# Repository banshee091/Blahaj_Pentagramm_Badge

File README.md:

# Blahaj_Pentagramm_Badge

Firmware:

Build WLED (https://github.com/Aircoookie/WLED) using PlatformIO with the following Environment using the Buildflags for BME280 and PIR:

```
[env:d1_mini]
...
build_flags = ${common.build_flags_esp8266} -D USERMOD_BME280 -D USERMOD_PIRSWITCH -D PIR_SENSOR_PIN=13
...
```

Configuration:
```
LED Preferences: 
    -> Length = 15
    -> GPIO = 14
Usermods:
    -> SDA = 4
    -> SCL = 5
    -> Enabled

    Reboot
```

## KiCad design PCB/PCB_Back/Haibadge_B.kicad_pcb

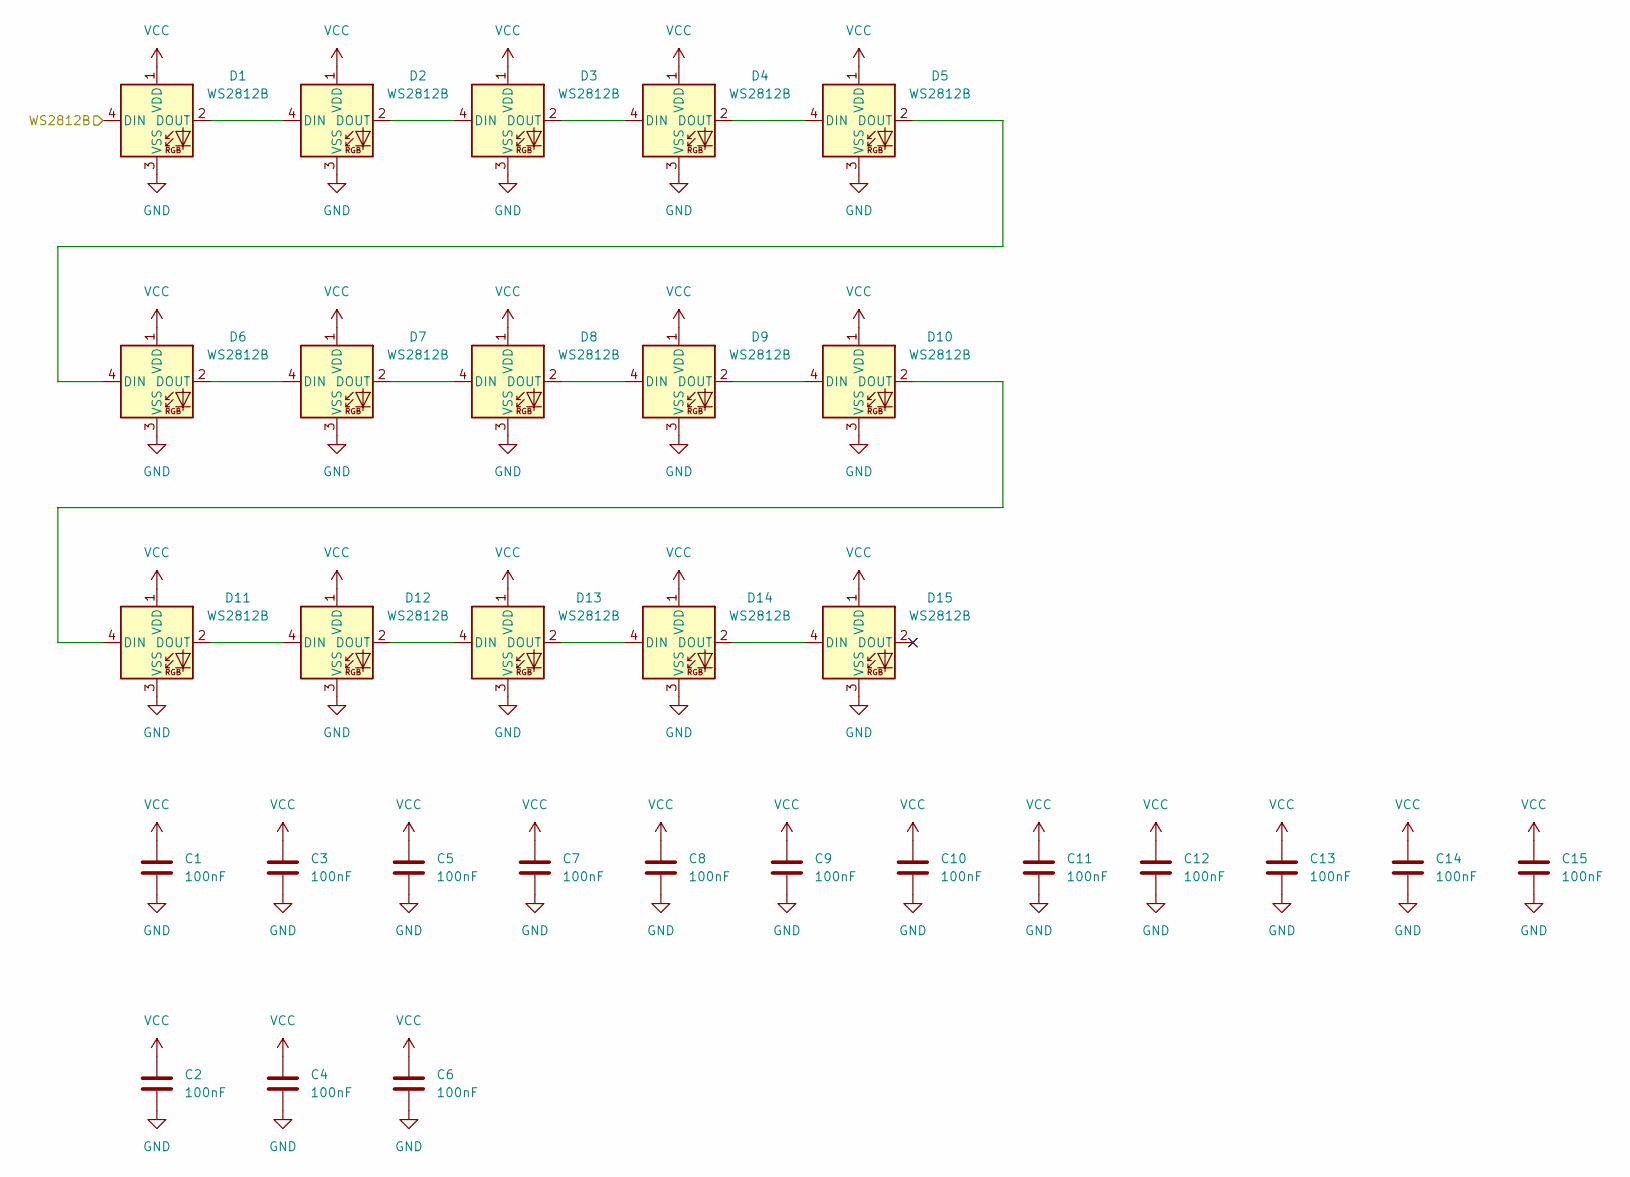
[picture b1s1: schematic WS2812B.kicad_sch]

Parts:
C1, C2, C3, C4, C5, C6, C7, C8, C9, C10, C11, C12, C13, C14, C15: 100nF; C_0805_2012Metric
D1, D2, D3, D4, D5, D6, D7, D8, D9, D10, D11, D12, D13, D14, D15: WS2812B; LED_WS2812B_PLCC4_5.0x5.0mm_P3.2mm

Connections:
/WS2812B/WS2812B: D1.4 (DIN); also elsewhere on the board
GND: C1.2, C2.2, C3.2, C4.2, C5.2, C6.2, C7.2, C8.2, C9.2, C10.2, C11.2, C12.2, C13.2, C14.2, C15.2, D1.3 (VSS), D2.3 (VSS), D3.3 (VSS), D4.3 (VSS), D5.3 (VSS), D6.3 (VSS), D7.3 (VSS), D8.3 (VSS), D9.3 (VSS), D10.3 (VSS), D11.3 (VSS), D12.3 (VSS), D13.3 (VSS), D14.3 (VSS), D15.3 (VSS); also elsewhere on the board
unnamed: D1.2 (DOUT), D2.4 (DIN)
unnamed: D2.2 (DOUT), D3.4 (DIN)
unnamed: D3.2 (DOUT), D4.4 (DIN)
unnamed: D4.2 (DOUT), D5.4 (DIN)
unnamed: D5.2 (DOUT), D6.4 (DIN)
unnamed: D6.2 (DOUT), D7.4 (DIN)
unnamed: D7.2 (DOUT), D8.4 (DIN)
unnamed: D8.2 (DOUT), D9.4 (DIN)
unnamed: D9.2 (DOUT), D10.4 (DIN)
unnamed: D10.2 (DOUT), D11.4 (DIN)
unnamed: D11.2 (DOUT), D12.4 (DIN)
unnamed: D12.2 (DOUT), D13.4 (DIN)
unnamed: D13.2 (DOUT), D14.4 (DIN)
unnamed: D14.2 (DOUT), D15.4 (DIN)
VCC: C1.1, C2.1, C3.1, C4.1, C5.1, C6.1, C7.1, C8.1, C9.1, C10.1, C11.1, C12.1, C13.1, C14.1, C15.1, D1.1 (VDD), D2.1 (VDD), D3.1 (VDD), D4.1 (VDD), D5.1 (VDD), D6.1 (VDD), D7.1 (VDD), D8.1 (VDD), D9.1 (VDD), D10.1 (VDD), D11.1 (VDD), D12.1 (VDD), D13.1 (VDD), D14.1 (VDD), D15.1 (VDD); also elsewhere on the board

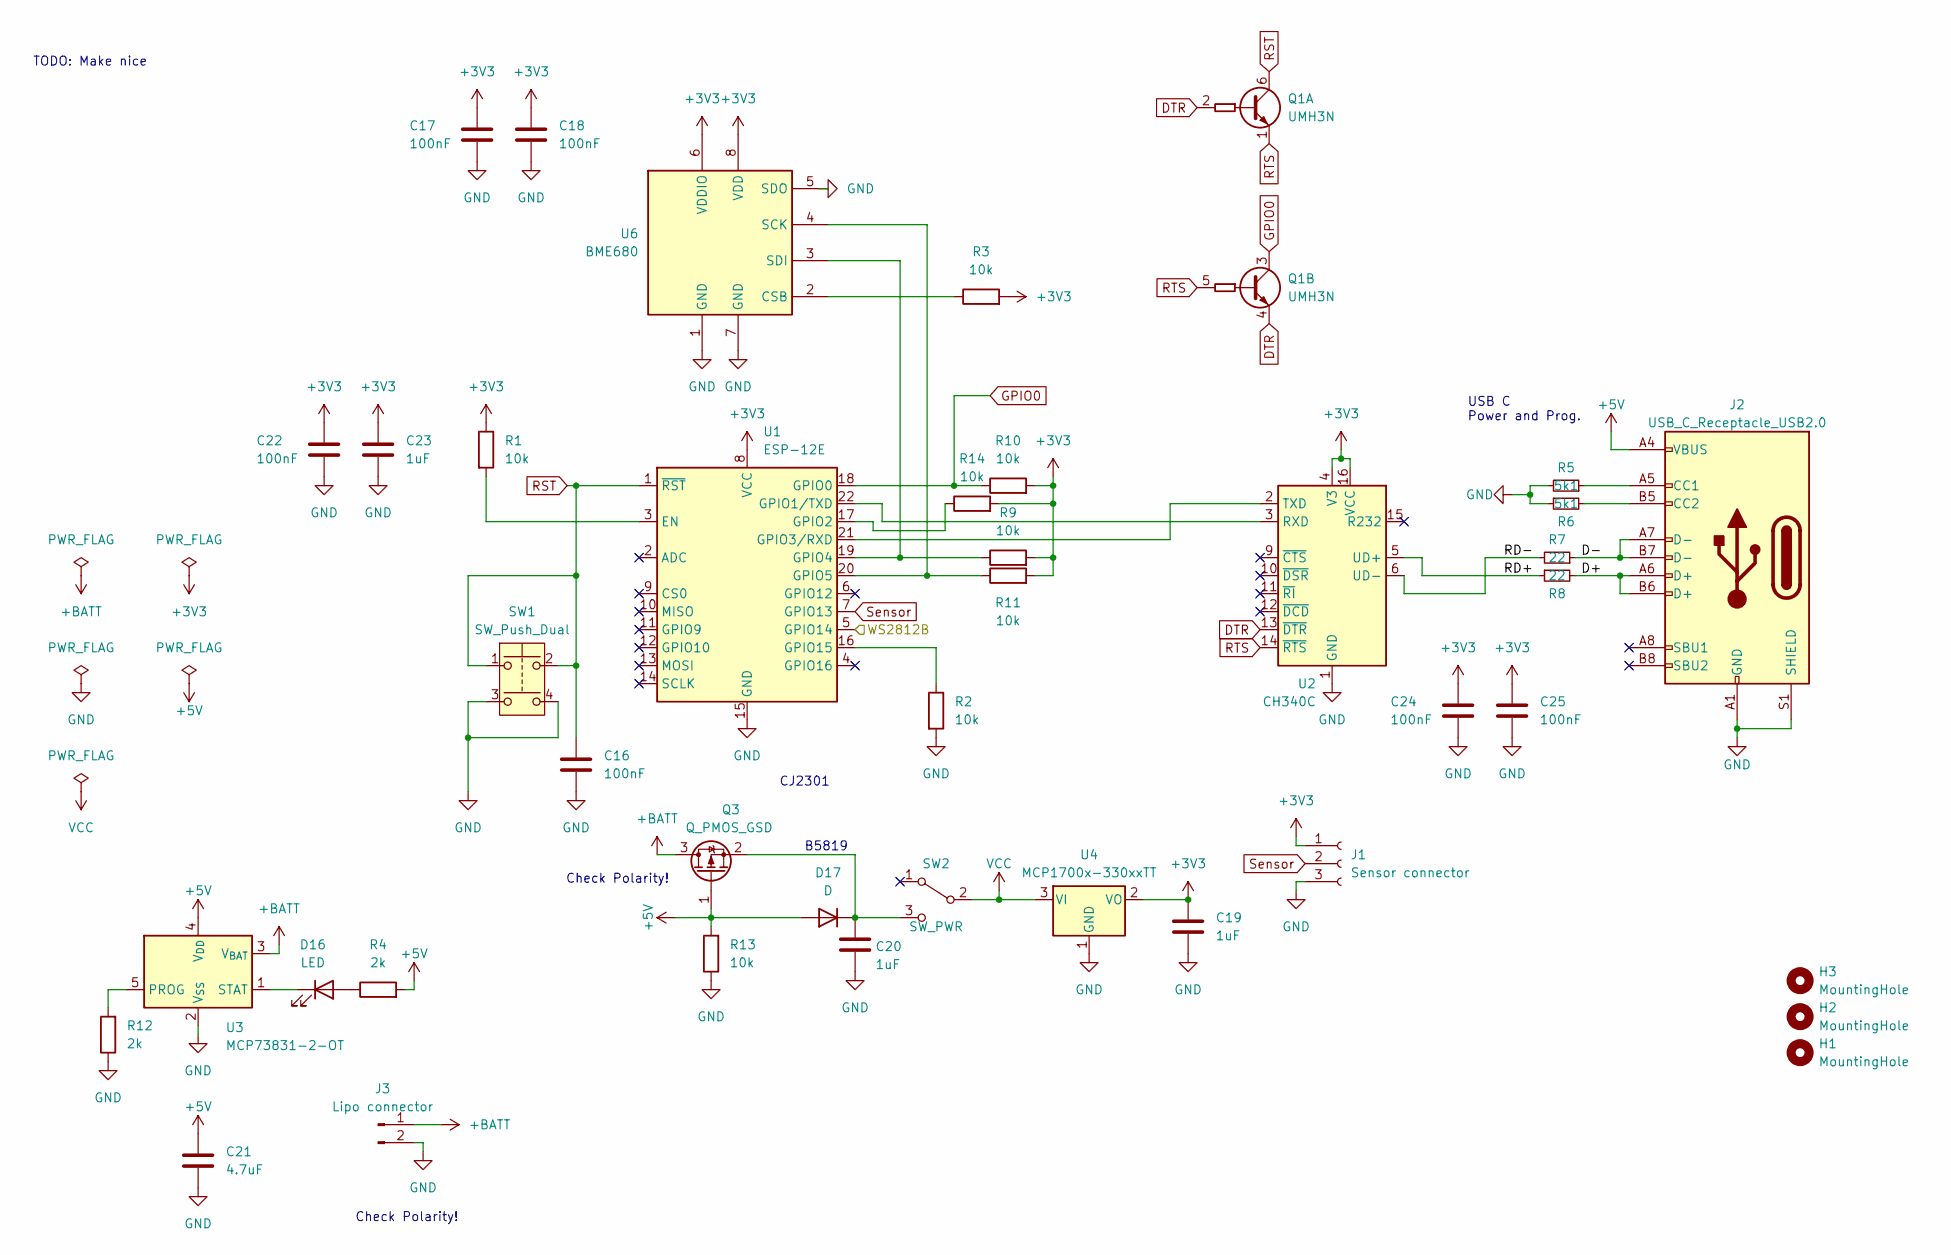
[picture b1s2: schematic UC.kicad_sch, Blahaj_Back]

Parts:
C16, C17, C18, C22, C24, C25: 100nF; C_0805_2012Metric
C19, C20, C23: 1uF; C_0805_2012Metric
C21: 4.7uF; C_0805_2012Metric
D16: LED; LED_1206_3216Metric
D17: D; D_SOD-323_HandSoldering
H1, H2, H3: MountingHole; MountingHole_2.7mm_M2.5
J1: Sensor connector; HDR-SMD_3P-P2.54-H-F-L11.5
J2: USB_C_Receptacle_USB2.0; USB_C_Receptacle_HRO_TYPE-C-31-M-12
J3: Lipo connector; JST_PH_S2B-PH-K_1x02_P2.00mm_Horizontal
Q1: UMH3N; SOT-363_SC-70-6
Q3: Q_PMOS_GSD; SOT-23
R1, R2, R3, R9, R10, R11, R13, R14: 10k; R_0805_2012Metric
R4, R12: 2k; R_0805_2012Metric
R5, R6: 5k1; R_0805_2012Metric
R7, R8: 22; R_0805_2012Metric
SW1: SW_Push_Dual; KH-6X6X6H-STM
SW2: SW_PWR; SW-SMD_MK-12C02-G025
U1: ESP-12E
U2: CH340C; SOIC-16_3.9x9.9mm_P1.27mm
U3: MCP73831-2-OT; SOT-23-5
U4: MCP1700x-330xxTT; SOT-23
U6: BME680; Bosch_LGA-8_3x3mm_P0.8mm_ClockwisePinNumbering

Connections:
+3V3: C17.1, C18.1, C19.1, C22.1, C23.1, C24.1, C25.1, J1.1, R1.1, R3.2, R9.2, R10.2, R11.2, R14.2, U1.8 (VCC), U2.4 (V3), U2.16 (VCC), U4.2 (VO), U6.6 (VDDIO), U6.8 (VDD)
+5V: C21.1, D17.2 (A), J2.A4 (VBUS), J2.A9 (VBUS), J2.B4 (VBUS), J2.B9 (VBUS), Q3.1 (G), R4.2, R13.2, U3.4 (V_{DD})
+BATT: J3.1, Q3.3 (D), U3.3 (V_{BAT})
/WS2812B/WS2812B: U1.5 (GPIO14); also elsewhere on the board
/uC/D+: J2.A6 (D+), J2.B6 (D+), R8.2
/uC/D-: J2.A7 (D-), J2.B7 (D-), R7.1
/uC/RD+: R8.1, U2.5 (UD+)
/uC/RD-: R7.2, U2.6 (UD-)
DTR: Q1.2 (B1), Q1.4 (E2), U2.13 (~DTR)
GND: C16.2, C17.2, C18.2, C19.2, C20.2, C21.2, C22.2, C23.2, C24.2, C25.2, J1.3, J2.A1 (GND), J2.A12 (GND), J2.B1 (GND), J2.B12 (GND), J2.S1 (SHIELD), J3.2, R2.2, R5.2, R6.1, R12.1, R13.1, SW1.3, SW1.4, U1.15 (GND), U2.1 (GND), U3.2 (V_{SS}), U4.1 (GND), U6.1 (GND), U6.5 (SDO), U6.7 (GND); also elsewhere on the board
GPIO0: Q1.3 (C2), R10.1, U1.18 (GPIO0)
unnamed: D16.2 (A), R4.1
unnamed: D16.1 (K), U3.1 (STAT)
unnamed: C20.1, D17.1 (K), Q3.2 (S), SW2.3 (C)
unnamed: J2.A5 (CC1), R5.1
unnamed: J2.B5 (CC2), R6.2
unnamed: R1.2, U1.3 (EN)
unnamed: U1.22 (GPIO1/TXD), U2.3 (RXD)
unnamed: R14.1, U1.17 (GPIO2)
unnamed: U1.21 (GPIO3/RXD), U2.2 (TXD)
unnamed: R9.1, U1.19 (GPIO4), U6.3 (SDI)
unnamed: R11.1, U1.20 (GPIO5), U6.4 (SCK)
unnamed: R2.1, U1.16 (GPIO15)
unnamed: R12.2, U3.5 (PROG)
unnamed: R3.1, U6.2 (CSB)
RST: C16.1, Q1.6 (C1), SW1.1, SW1.2, U1.1 (~RST)
RTS: Q1.1 (E1), Q1.5 (B2), U2.14 (~RTS)
Sensor: J1.2, U1.7 (GPIO13)
VCC: SW2.2 (B), U4.3 (VI); also elsewhere on the board

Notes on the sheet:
TODO: Make nice
Check Polarity!
Check Polarity!
USB C Power and Prog.
B5819
CJ2301

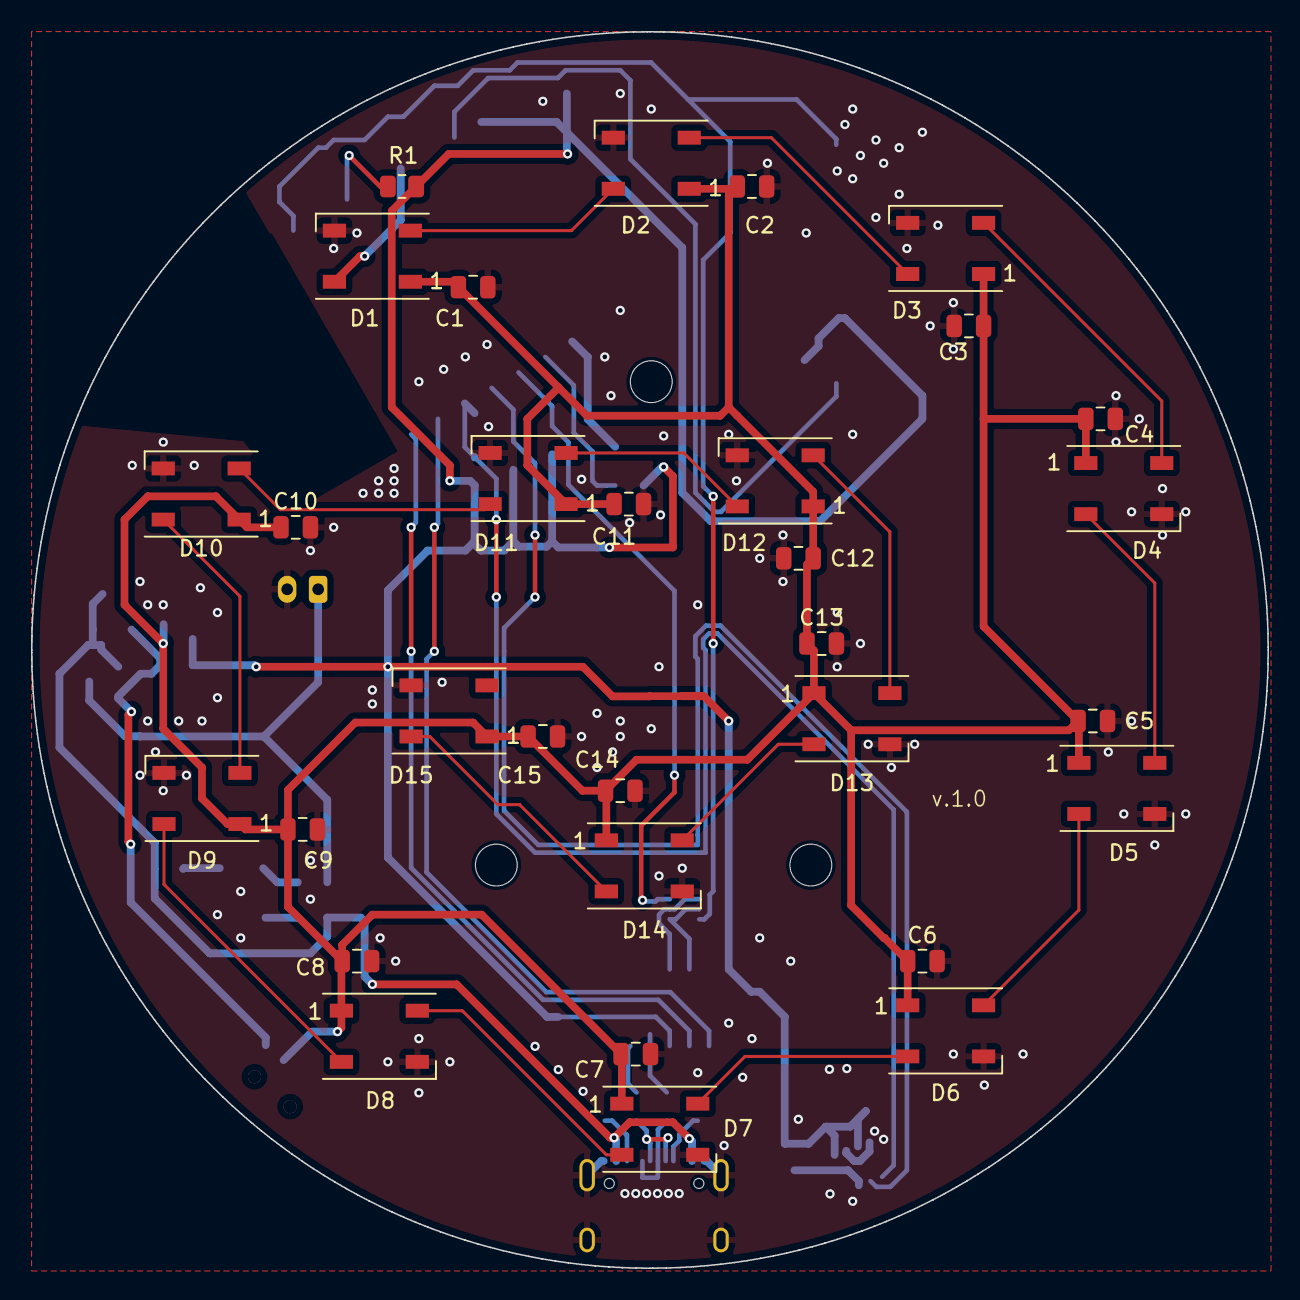
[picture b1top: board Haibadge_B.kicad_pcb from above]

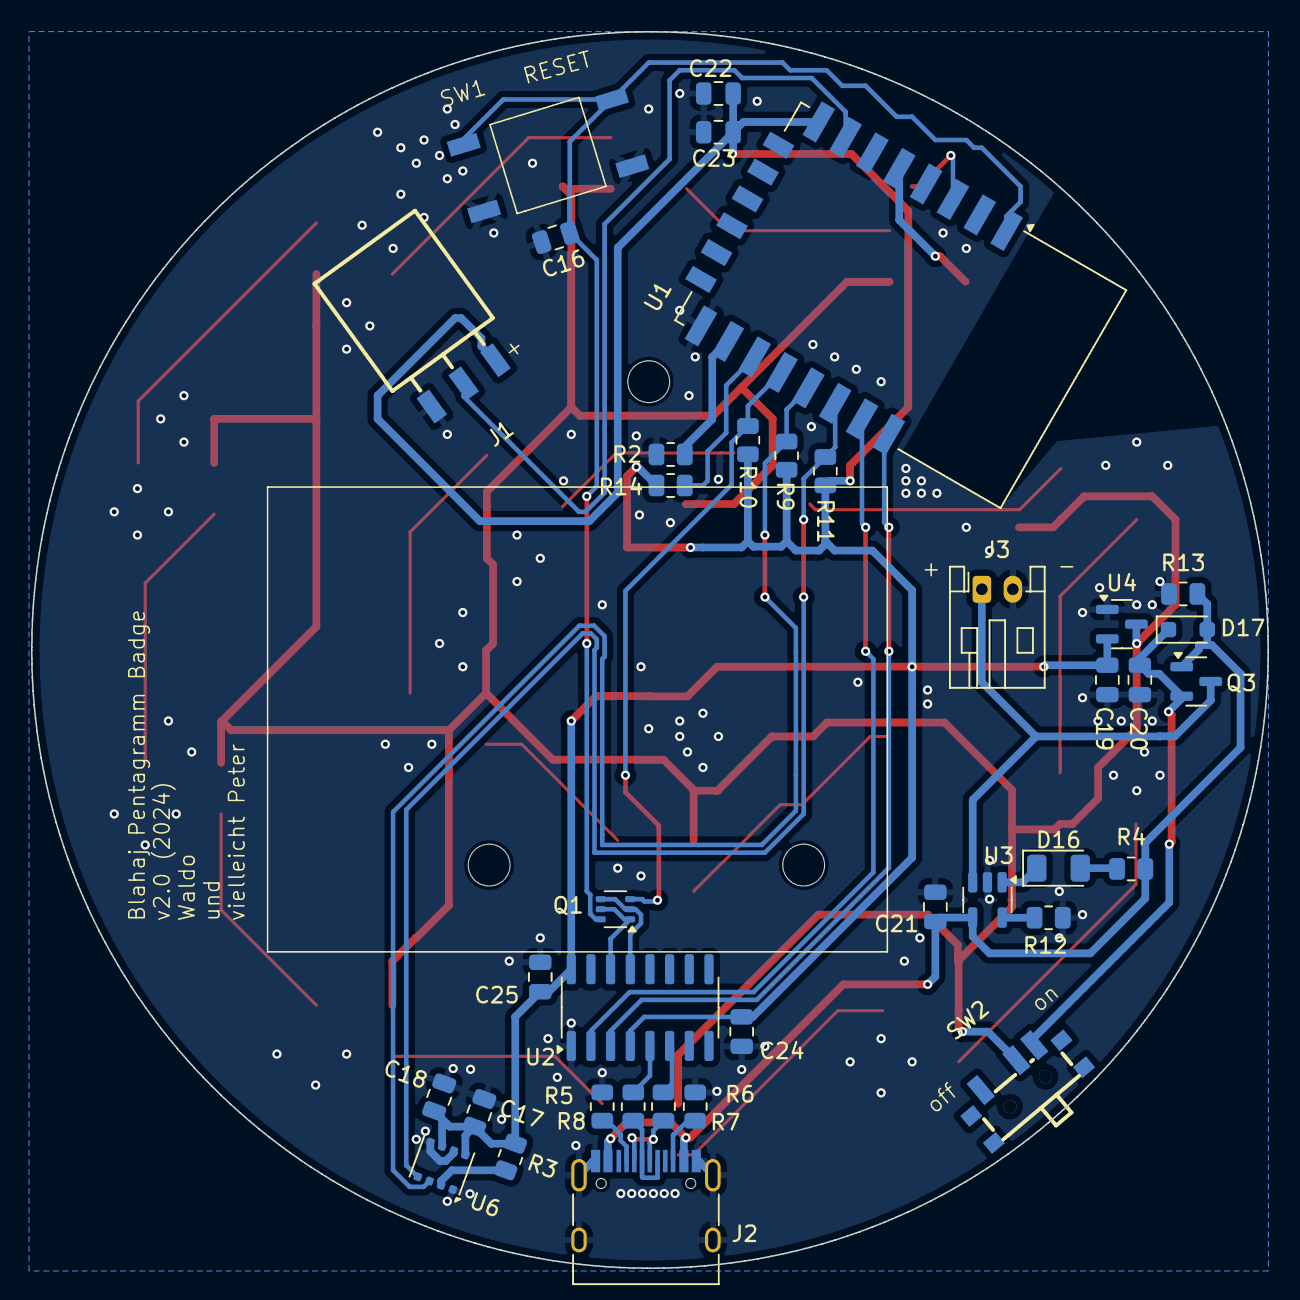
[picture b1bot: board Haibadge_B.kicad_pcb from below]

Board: 2 copper layers, 79.8 x 79.8 mm, 71 parts (37 on the bottom side), 43 nets.

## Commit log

2024-08-02 Init
2024-08-03 Layout, Routing, Stuff
2024-08-04 Label placements, Misc Fixes, Partslist
2024-08-09 Misc. Fixes, v1.0.
2024-08-26 Added production Files
2024-09-02 Switched D+/D-, TX/RX, Switch Pins and rotated Lipo Marking
2024-09-03 Moved Sensor Connector (make Room for Lipo) and Align with Pentagram Angle
2024-09-07 Moved Sensor again (inset), Work on Case
2024-09-07 Added R14 10k Pullup to GPIO2
2024-09-08 Update gitignore
2024-09-08 Added Frontplate with Transparent Text and Silver Rim, Cleanup
2024-09-08 Switched D16 Resistor from 1k to 2k
2024-09-14 Change J1 to SMD, Production
2024-09-26 Fixed Typo, added new ibom
2024-09-30 Revert "Fixed Typo, added new ibom"
    This reverts commit 21eb23da6b9f4b1b78e37bb966b9e164ecd6150b.
2024-12-23 Added STL
2025-01-10 add configuration to readme
2025-02-11 Made more things transparent
2025-02-11 Added Plus for Sensor
2025-02-21 Revert "WIP"
    This reverts commit bec9596e63e47101addb2355b0aaca8e1697c271.
2025-03-29 Production Samples
    TODO: Border for working sample to narrow.
2025-04-01 Back corrections, Front Edge Cut bigger.
2025-07-11 Production ready commit
    Production Version 3 commit
